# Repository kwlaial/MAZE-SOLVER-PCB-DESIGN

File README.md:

# MAZE-SOLVER-PCB-DESIGN

My first PCB designed with STM32 to solve a maze by line following

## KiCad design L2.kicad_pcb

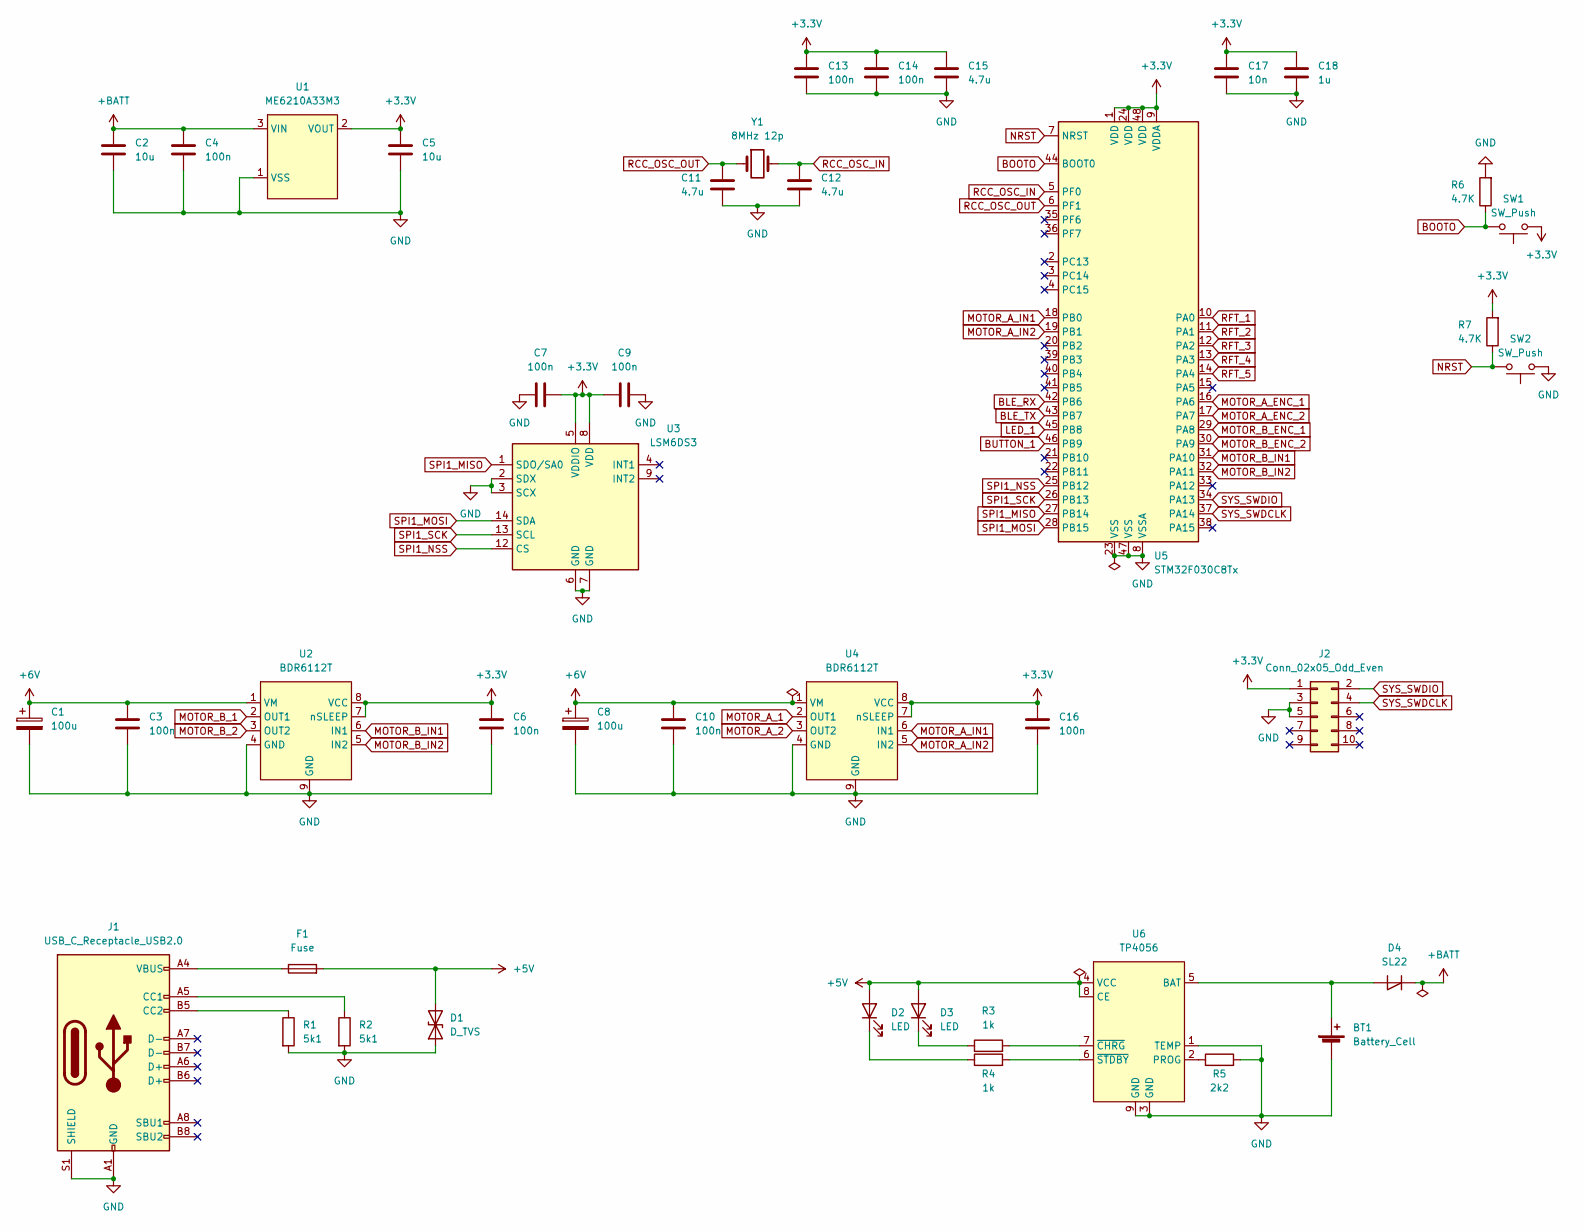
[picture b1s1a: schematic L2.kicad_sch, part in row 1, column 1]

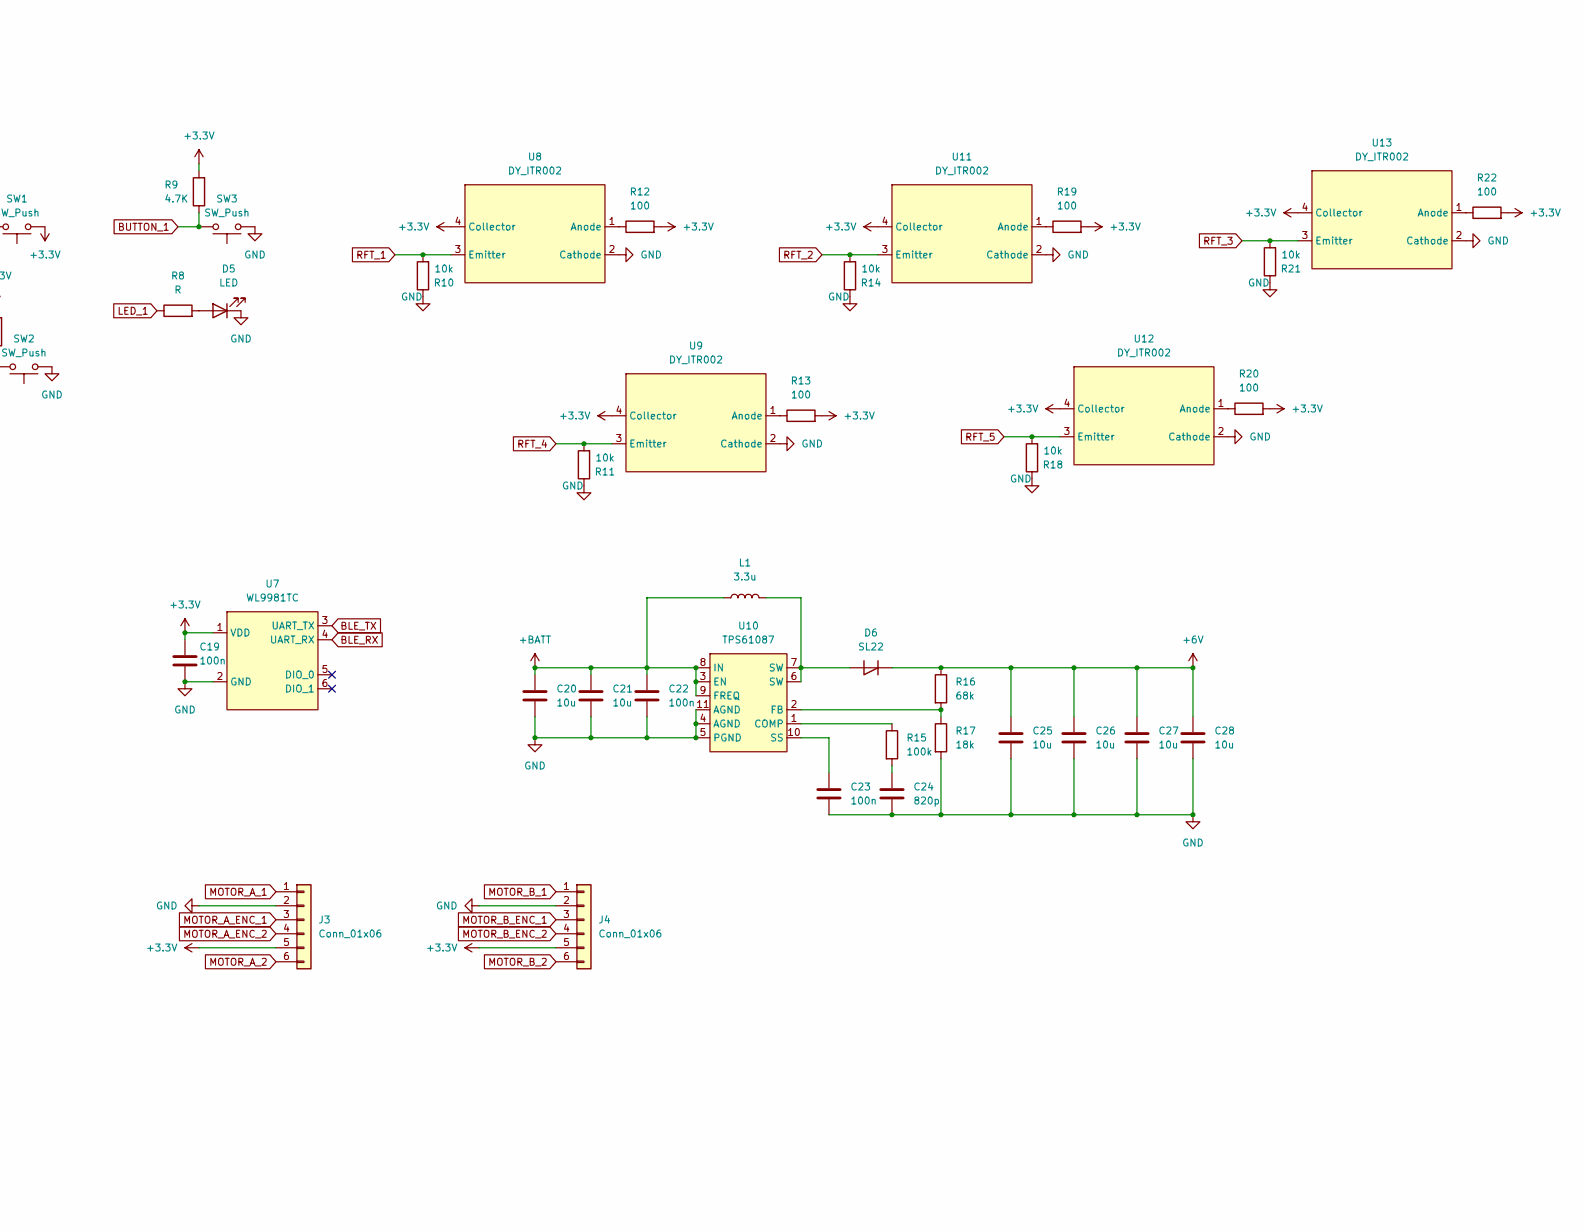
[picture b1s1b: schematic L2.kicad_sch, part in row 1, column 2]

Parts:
BT1: Battery_Cell; BatteryHolder_MPD_BH-18650-PC2
C1, C8: 100u; CP_EIA-7343-31_Kemet-D_Pad2.25x2.55mm_HandSolder
C2, C5, C20, C21, C25, C26, C27, C28: 10u; C_0805_2012Metric_Pad1.18x1.45mm_HandSolder
C3, C4, C6, C7, C9, C10, C13, C14, C16, C19, C22, C23: 100n; C_0805_2012Metric_Pad1.18x1.45mm_HandSolder
C11, C12, C15: 4.7u; C_0805_2012Metric_Pad1.18x1.45mm_HandSolder
C17: 10n; C_0805_2012Metric_Pad1.18x1.45mm_HandSolder
C18: 1u; C_0805_2012Metric_Pad1.18x1.45mm_HandSolder
C24: 820p; C_0805_2012Metric_Pad1.18x1.45mm_HandSolder
D1: D_TVS; D_SMB_Handsoldering
D2, D3, D5: LED; LED_0805_2012Metric_Pad1.15x1.40mm_HandSolder
D4, D6: SL22; D_SMB_Handsoldering
F1: Fuse; Fuse_1812_4532Metric_Pad1.30x3.40mm_HandSolder
J1: USB_C_Receptacle_USB2.0; USB_C_Receptacle_HRO_TYPE-C-31-M-12
J2: Conn_02x05_Odd_Even; PinHeader_2x05_P1.27mm_Vertical
J3, J4: Conn_01x06; PinHeader_1x06_P2.54mm_Vertical
L1: 3.3u; 5.2x5.7x2.8mm
R1, R2: 5k1; R_0805_2012Metric_Pad1.20x1.40mm_HandSolder
R3, R4: 1k; R_0805_2012Metric_Pad1.20x1.40mm_HandSolder
R5: 2k2; R_0805_2012Metric_Pad1.20x1.40mm_HandSolder
R6, R7, R9: 4.7K; R_0805_2012Metric_Pad1.20x1.40mm_HandSolder
R8: R; R_0805_2012Metric_Pad1.20x1.40mm_HandSolder
R10, R11, R14, R18, R21: 10k; R_0805_2012Metric_Pad1.20x1.40mm_HandSolder
R12, R13, R19, R20, R22: 100; R_0805_2012Metric_Pad1.20x1.40mm_HandSolder
R15: 100k; R_0805_2012Metric_Pad1.20x1.40mm_HandSolder
R16: 68k; R_0805_2012Metric_Pad1.20x1.40mm_HandSolder
R17: 18k; R_0805_2012Metric_Pad1.20x1.40mm_HandSolder
SW1, SW2, SW3: SW_Push; SW_SPST_SKQG_WithStem
U1: ME6210A33M3; SOT-23
U2, U4: BDR6112T; SOIC-8-1EP_3.9x4.9mm_P1.27mm_EP2.29x3mm
U3: LSM6DS3; LGA-14_3x2.5mm_P0.5mm_LayoutBorder3x4y
U5: STM32F030C8Tx; LQFP-48_7x7mm_P0.5mm
U6: TP4056; SOIC-8-1EP_3.9x4.9mm_P1.27mm_EP2.29x3mm
U7: WL9981TC; WL9981
U8, U9, U11, U12, U13: DY_ITR002; DY-ITR002
U10: TPS61087; VSON-10-1EP_3x3mm_P0.5mm_EP1.2x2mm
Y1: 8MHz 12p; Crystal_SMD_5032-2Pin_5.0x3.2mm

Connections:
+3V3: C5.1, C6.1, C7.2, C9.1, C13.1, C14.1, C15.1, C16.1, C17.1, C18.1, C19.1, J2.1, J3.5, J4.5, R7.2, R9.2, R12.2, R13.2, R19.2, R20.2, R22.2, SW1.1, U1.2 (VOUT), U2.7 (nSLEEP), U2.8 (VCC), U3.5 (VDDIO), U3.8 (VDD), U4.7 (nSLEEP), U4.8 (VCC), U5.1 (VDD), U5.9 (VDDA), U5.24 (VDD), U5.48 (VDD), U7.1 (VDD), U8.4 (Collector), U9.4 (Collector), U11.4 (Collector), U12.4 (Collector), U13.4 (Collector)
+5V: D1.2 (A2), D2.2 (A), D3.2 (A), F1.2, U6.4 (VCC), U6.8 (CE)
+6V: C1.1, C3.1, C8.1, C10.1, C25.2, C26.1, C27.1, C28.1, D6.1 (K), R16.1, U2.1 (VM), U4.1 (VM)
+BATT: C2.1, C4.1, C20.1, C21.1, C22.1, D4.1 (K), L1.1, U1.3 (VIN), U10.3 (EN), U10.8 (IN), U10.9 (FREQ)
BLE_RX: U5.42 (PB6), U7.4 (UART_RX)
BLE_TX: U5.43 (PB7), U7.3 (UART_TX)
BOOTO: R6.1, SW1.2, U5.44 (BOOT0)
BUTTON_1: R9.1, SW3.2, U5.46 (PB9)
GND: BT1.2 (-), C1.2, C2.2, C3.2, C4.2, C5.2, C6.2, C7.1, C8.2, C9.2, C10.2, C11.2, C12.2, C13.2, C14.2, C15.2, C16.2, C17.2, C18.2, C19.2, C20.2, C21.2, C22.2, C23.2, C24.2, C25.1, C26.2, C27.2, C28.2, D1.1 (A1), D5.1 (K), J1.A1 (GND), J1.A12 (GND), J1.B1 (GND), J1.B12 (GND), J1.S1 (SHIELD), J2.3, J2.5, J3.2, J4.2, R1.2, R2.2, R5.2, R6.2, R10.1, R11.1, R14.1, R17.2, R18.1, R21.1, SW2.1, SW3.1, U1.1 (VSS), U2.4 (GND), U2.9 (GND), U3.2 (SDX), U3.3 (SCX), U3.6 (GND), U3.7 (GND), U4.4 (GND), U4.9 (GND), U5.8 (VSSA), U5.23 (VSS), U5.47 (VSS), U6.1 (TEMP), U6.3 (GND), U6.9 (GND), U7.2 (GND), U8.2 (Cathode), U9.2 (Cathode), U10.4 (AGND), U10.5 (PGND), U10.11 (AGND), U11.2 (Cathode), U12.2 (Cathode), U13.2 (Cathode)
LED_1: R8.1, U5.45 (PB8)
MOTOR_A_1: J3.1, U4.2 (OUT1)
MOTOR_A_2: J3.6, U4.3 (OUT2)
MOTOR_A_ENC_1: J3.3, U5.16 (PA6)
MOTOR_A_ENC_2: J3.4, U5.17 (PA7)
MOTOR_A_IN1: U4.6 (IN1), U5.18 (PB0)
MOTOR_A_IN2: U4.5 (IN2), U5.19 (PB1)
MOTOR_B_1: J4.1, U2.2 (OUT1)
MOTOR_B_2: J4.6, U2.3 (OUT2)
MOTOR_B_ENC_1: J4.3, U5.29 (PA8)
MOTOR_B_ENC_2: J4.4, U5.30 (PA9)
MOTOR_B_IN1: U2.6 (IN1), U5.31 (PA10)
MOTOR_B_IN2: U2.5 (IN2), U5.32 (PA11)
NRST: R7.1, SW2.2, U5.7 (NRST)
unnamed: BT1.1 (+), D4.2 (A), U6.5 (BAT)
unnamed: C23.1, U10.10 (SS)
unnamed: C24.1, R15.2
unnamed: D2.1 (K), R4.1
unnamed: D3.1 (K), R3.1
unnamed: D5.2 (A), R8.2
unnamed: D6.2 (A), L1.2, U10.6 (SW), U10.7 (SW)
unnamed: F1.1, J1.A4 (VBUS), J1.A9 (VBUS), J1.B4 (VBUS), J1.B9 (VBUS)
unnamed: J1.A5 (CC1), R2.1
unnamed: J1.B5 (CC2), R1.1
unnamed: R3.2, U6.7 (~CHRG)
unnamed: R4.2, U6.6 (~STDBY)
unnamed: R5.1, U6.2 (PROG)
unnamed: R12.1, U8.1 (Anode)
unnamed: R13.1, U9.1 (Anode)
unnamed: R15.1, U10.1 (COMP)
unnamed: R16.2, R17.1, U10.2 (FB)
unnamed: R19.1, U11.1 (Anode)
unnamed: R20.1, U12.1 (Anode)
unnamed: R22.1, U13.1 (Anode)
RCC_OSC_IN: C12.1, U5.5 (PF0), Y1.2
RCC_OSC_OUT: C11.1, U5.6 (PF1), Y1.1
RFT_1: R10.2, U5.10 (PA0), U8.3 (Emitter)
RFT_2: R14.2, U5.11 (PA1), U11.3 (Emitter)
RFT_3: R21.2, U5.12 (PA2), U13.3 (Emitter)
RFT_4: R11.2, U5.13 (PA3), U9.3 (Emitter)
RFT_5: R18.2, U5.14 (PA4), U12.3 (Emitter)
SPI1_MISO: U3.1 (SDO/SA0), U5.27 (PB14)
SPI1_MOSI: U3.14 (SDA), U5.28 (PB15)
SPI1_NSS: U3.12 (CS), U5.25 (PB12)
SPI1_SCK: U3.13 (SCL), U5.26 (PB13)
SYS_SWDCLK: J2.4, U5.37 (PA14)
SYS_SWDIO: J2.2, U5.34 (PA13)

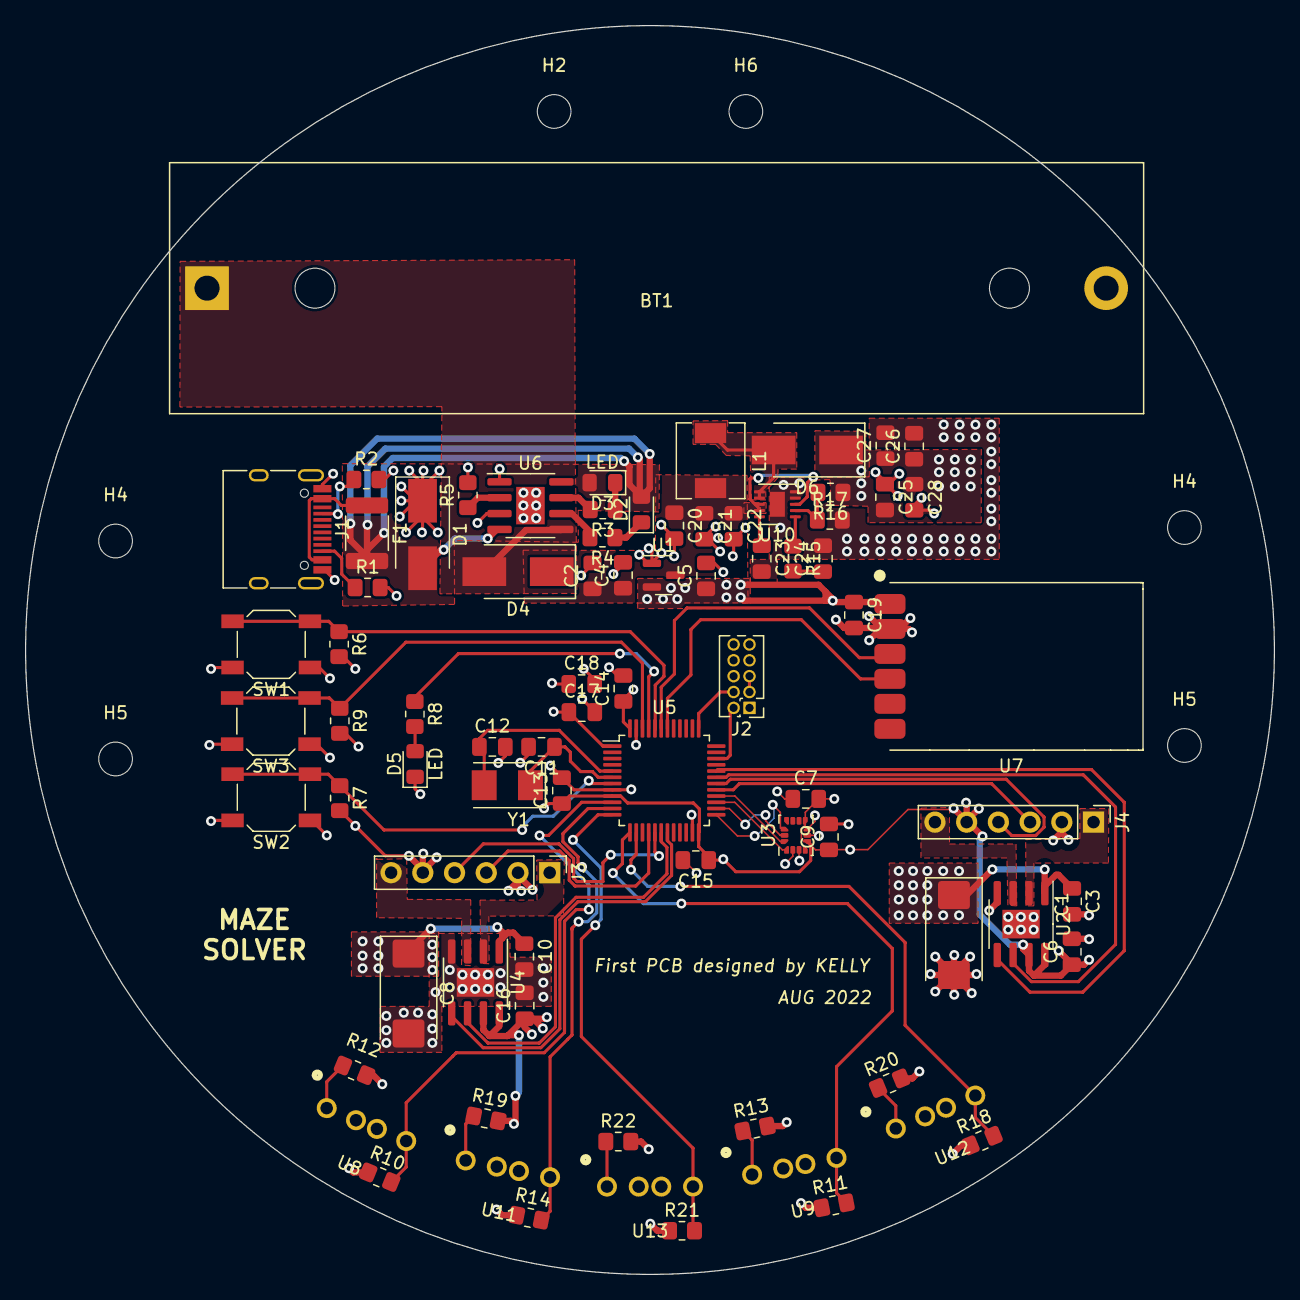
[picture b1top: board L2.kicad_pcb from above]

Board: 4 copper layers, 100.0 x 100.0 mm, 86 parts (0 on the bottom side), 56 nets.

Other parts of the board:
H2, H4, H4#2, H5, H5#2, H6: MountingHole; MountingHole_2.7mm
